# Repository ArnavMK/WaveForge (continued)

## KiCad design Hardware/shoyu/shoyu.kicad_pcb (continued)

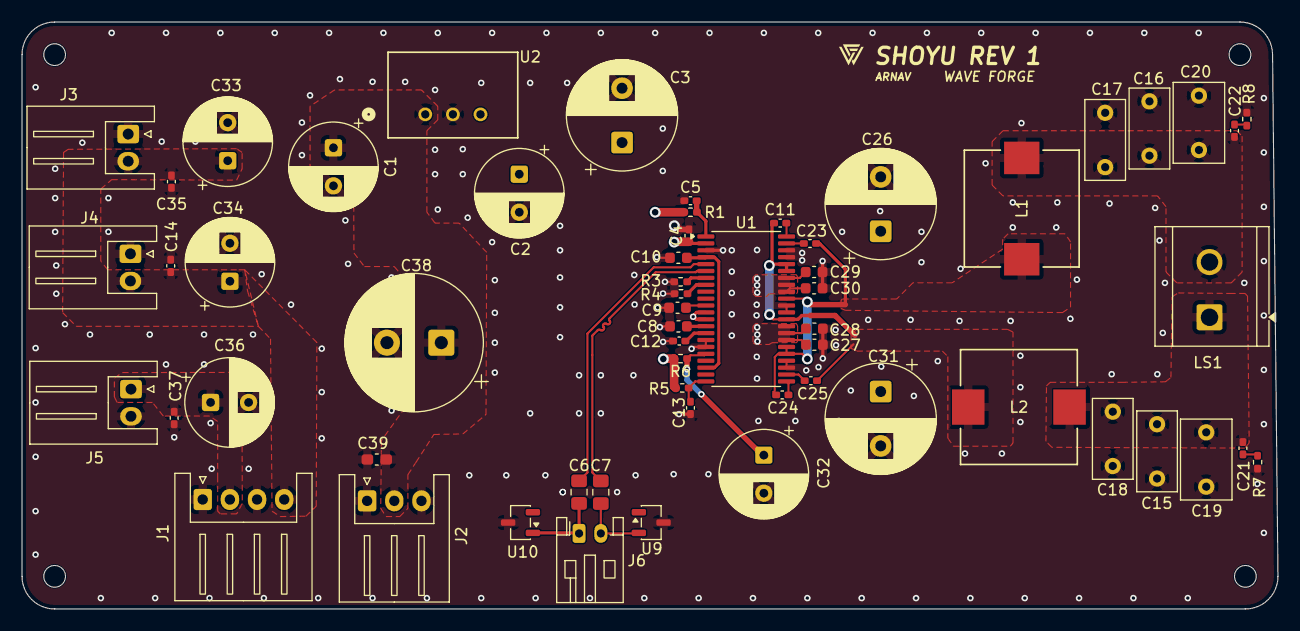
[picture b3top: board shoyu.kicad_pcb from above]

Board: 4 copper layers, 115.6 x 54.0 mm, 63 parts (0 on the bottom side), 28 nets.

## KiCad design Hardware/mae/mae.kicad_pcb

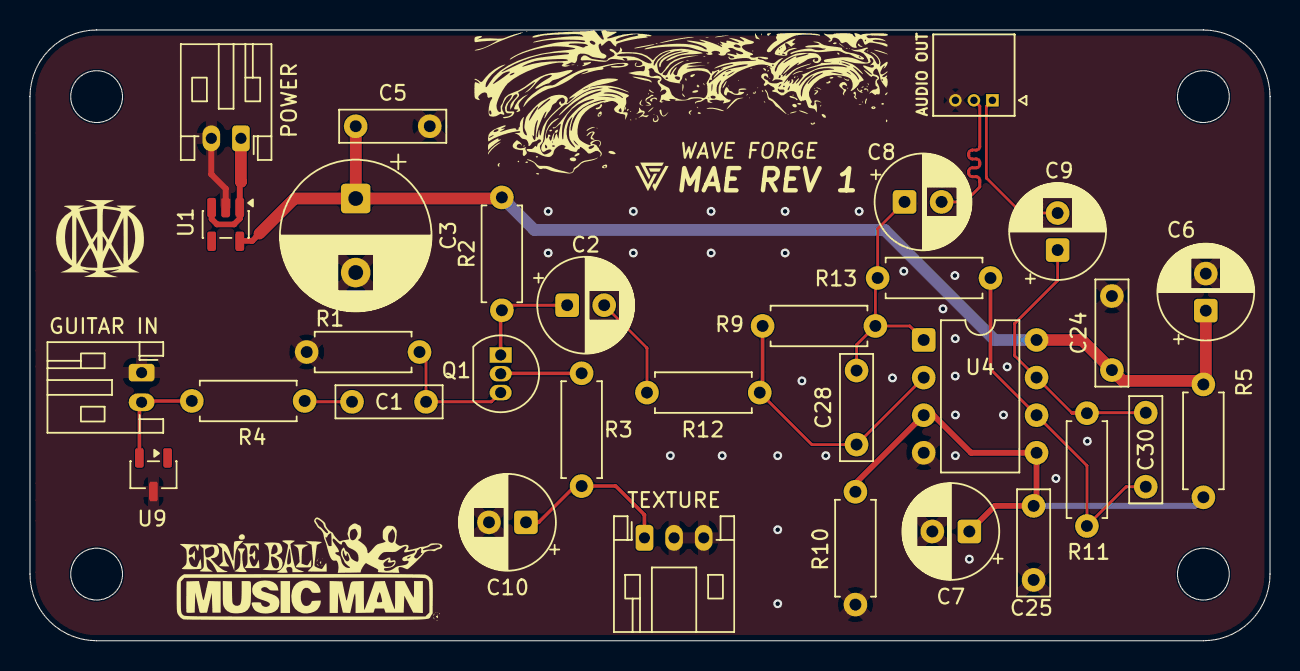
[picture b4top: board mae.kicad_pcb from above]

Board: 2 copper layers, 83.8 x 41.2 mm, 35 parts (0 on the bottom side), 17 nets.

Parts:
AUDIO OUT: 530480310; MOLEX_530480310
C1, C5, C24, C25: 100nF; C_Rect_L7.0mm_W2.0mm_P5.00mm
C2, C6, C7, C8, C9: 10uF; CP_Radial_D6.3mm_P2.50mm
C3: 100uF; CP_Radial_D10.0mm_P5.00mm
C10: c; CP_Radial_D6.3mm_P2.50mm
C28, C30: 100pF; C_Rect_L7.0mm_W2.0mm_P5.00mm
GUITAR IN: Guitar_IN; JST_PH_S2B-PH-K_1x02_P2.00mm_Horizontal
H3, H4, H5, H6: MountingHole; MountingHole_3.5mm
POWER: POWER_IN; JST_PH_S2B-PH-K_1x02_P2.00mm_Horizontal
Q1: Q_NJFET_DSG; TO-92_Inline
R1: 1MΩ; R_Axial_DIN0207_L6.3mm_D2.5mm_P7.62mm_Horizontal
R2, R3: R; R_Axial_DIN0207_L6.3mm_D2.5mm_P7.62mm_Horizontal
R4: 100Ω; R_Axial_DIN0207_L6.3mm_D2.5mm_P7.62mm_Horizontal
R5, R9, R10, R11, R12, R13: 10K; R_Axial_DIN0207_L6.3mm_D2.5mm_P7.62mm_Horizontal
TEXTURE: R_Potentiometer; JST_PH_S3B-PH-K_1x03_P2.00mm_Horizontal
U1: MAX40200AUK; SOT-23-5
U4: NE5532; DIP-8_W7.62mm
U9: SOT-23-3

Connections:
+9V: C3.1, C5.1, C6.1, C24.1, R2.2, R5.1, U1.5 (OUT), U4.8 (V+)
/AUDIO_OUT+: AUDIO OUT.2, C8.2
/AUDIO_OUT-: AUDIO OUT.1, C9.2
/DRAIN: C2.1, Q1.1 (D), R2.1
/GATE: C1.2, Q1.3 (G), R1.2
/PREAMP_OUT: C2.2, R12.1
/SOURCE: Q1.2 (S), R3.2
/U4A_AUDIO: C8.1, C28.2, R9.2, R13.1, U4.1
/VBIAS: C7.1, C25.1, R5.2, R10.2, U4.3 (+), U4.5 (+)
GND: AUDIO OUT.3, C3.2, C5.2, C6.2, C7.2, C10.2, C24.2, C25.2, GUITAR IN.1, POWER.2, R1.1, R10.1, TEXTURE.2, TEXTURE.3, U1.2 (GND), U4.4 (V-), U9.3 (GND)
unnamed: C1.1, R4.2
unnamed: C10.1, R3.1, TEXTURE.1
unnamed: C9.1, C30.2, R11.2, U4.7
unnamed: GUITAR IN.2, R4.1, U9.2 (IO2)
unnamed: POWER.1, U1.1 (VDD), U1.3 (EN)
unnamed: C28.1, R9.1, R12.2, U4.2 (-)
unnamed: C30.1, R11.1, R13.2, U4.6 (-)

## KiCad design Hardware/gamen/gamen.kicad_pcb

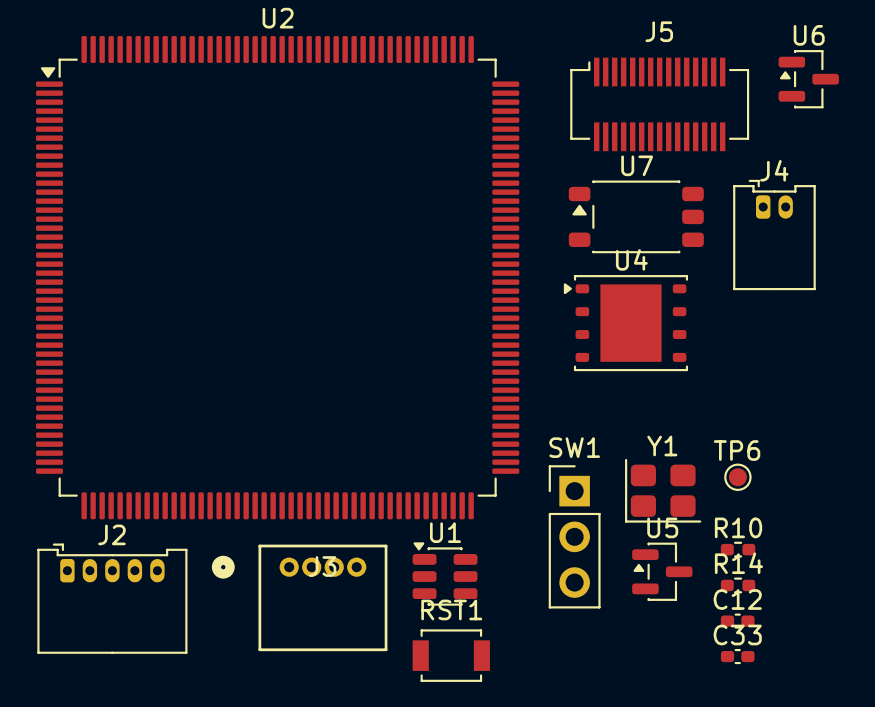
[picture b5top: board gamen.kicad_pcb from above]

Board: 6 copper layers, 19 parts (1 on the bottom side), 56 nets, no tracks yet.

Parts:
C12, C33: 100nF; C_0402_1005Metric_Pad0.74x0.62mm_HandSolder
J2: Conn_01x05_Pin; Molex_PicoBlade_53048-0510_1x05_P1.25mm_Horizontal
J3: UART_Header; CONN04_530480410_MOL
J4: MIDI CONN; Molex_PicoBlade_53048-0210_1x02_P1.25mm_Horizontal
J5: SCREEN CONN; Hirose_DF12_DF12C3.0-30DS-0.5V_2x15_P0.50mm_Vertical
R10, R14: 100Ω; R_0402_1005Metric_Pad0.72x0.64mm_HandSolder
RST1: SW_Push; SW_SPST_B3U-1000P
SW1: SW_SPDT; PinHeader_1x03_P2.54mm_Vertical
TP6: TP_UARTTX; TestPoint_Pad_D1.0mm
U1: TPS562201DDCR; SOT-23-6
U2: STM32H743IITx; LQFP-176_24x24mm_P0.5mm
U3: AS4C16M16SA-6TIN; TSOP-II-54_22.2x10.16mm_P0.8mm
U4: W25Q256JWPIQ; WSON-8-1EP_6x5mm_P1.27mm_EP3.4x4.3mm
U5, U6: SOT-23
U7: TLP2361(E; SO-5-6_4.55x3.7mm_P1.27mm
Y1: 25MHz; Crystal_SMD_WE_CFPX-180-4Pin_3.2x2.5mm

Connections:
+3.3V: C33.1, J2.5, J3.1, J5.4, SW1.3 (C), U2.6 (VBAT), U2.15 (VDD), U2.23 (VDD), U2.36 (VDD), U2.49 (VDD), U2.62 (VDD), U2.72 (VDD), U2.82 (VDD), U2.91 (VDD), U2.103 (VDD), U2.114 (VDD33_USB), U2.127 (VDD), U2.136 (VDD), U2.149 (VDD), U2.159 (VDD), U2.172 (VDD), U3.1 (VDD), U3.3 (VDDQ), U3.9 (VDDQ), U3.14 (VDD), U3.27 (VDD), U3.43 (VDDQ), U3.49 (VDDQ), U4.8 (VCC), U7.6 (VDD)
+3.3VA: U2.38 (VREF+), U2.39 (VDDA)
+5V: J5.1, J5.2, U1.3 (VIN), U1.5 (EN), U6.1 (IO1), U6.2 (IO2)
/MIDI_GND: J4.1, U7.3 (K)
/NRST: C12.1, J2.2, RST1.1, U2.31 (NRST)
/OSC_IN: U2.29 (PH0), Y1.3
/OSC_OUT: U2.30 (PH1), Y1.1
/QSPI_CLK: U2.28 (PF10), U4.6 (CLK)
/QSPI_IO0: U2.27 (PF9), U4.5 (DI/IO_{0})
/QSPI_IO1: U2.26 (PF8), U4.2 (DO/IO_{1})
/QSPI_IO2: U2.25 (PF7), U4.3 (~WP/IO_{2})
/QSPI_IO3: U2.24 (PF6), U4.7 (~HOLD/~RESET/IO_{3})
/SDNIS_RAS: U2.59 (PF11), U3.18 (*RAS)
/SDRAM_A0: U2.16 (PF0), U3.23 (A0)
/SDRAM_A1: U2.17 (PF1), U3.24 (A1)
/SDRAM_A2: U2.18 (PF2), U3.25 (A2)
/SDRAM_A3: U2.19 (PF3), U3.26 (A3)
/SDRAM_A4: U2.20 (PF4), U3.29 (A4)
/SDRAM_A5: U2.21 (PF5), U3.30 (A5)
/SDRAM_A6: U2.60 (PF12), U3.31 (A6)
/SDRAM_A7: U2.63 (PF13), U3.32 (A7)
/SDRAM_A8: U2.64 (PF14), U3.33 (A8)
/SDRAM_A9: U2.65 (PF15), U3.34 (A9)
/SDRAM_A10: U2.66 (PG0), U3.22 (A10/AP)
/SDRAM_A11: U2.67 (PG1), U3.35 (A11)
/SDRAM_A12: U2.106 (PG2), U3.36 (A12)
/SDRAM_BA0: U2.108 (PG4), U3.20 (BA0)
/SDRAM_BA1: U2.109 (PG5), U3.21 (BA1)
/SDRAM_CAS: U2.160 (PG15), U3.17 (*CAS)
/SDRAM_CKE: U2.35 (PC3_C), U3.37 (CKE)
/SDRAM_CLK: U2.112 (PG8), U3.38 (CLK)
/SDRAM_CS: U2.34 (PC2_C), U3.19 (*CS)
/SDRAM_DQ0: U2.104 (PD14), U2.142 (PD0), U3.2 (DQ0)
/SDRAM_DQ1: U2.105 (PD15), U3.4 (DQ1)
/SDRAM_DQ3: U2.143 (PD1), U3.7 (DQ3)
/SDRAM_DQ4: U2.70 (PE9), U3.8 (DQ4)
/SDRAM_DQ5: U2.69 (PE8), U3.10 (DQ5)
/SDRAM_DQ6: U2.68 (PE7), U3.11 (DQ6)
/SDRAM_DQ7: U2.73 (PE10), U3.13 (DQ7)
/SDRAM_DQ8: U2.74 (PE11), U3.42 (DQ8)
/SDRAM_DQ9: U2.75 (PE12), U3.44 (DQ9)
/SDRAM_DQ10: U2.76 (PE13), U3.45 (DQ10)
/SDRAM_DQ11: U2.77 (PE14), U3.47 (DQ11)
/SDRAM_DQ12: U2.78 (PE15), U3.48 (DQ12)
/SDRAM_DQ13: U2.96 (PD8), U3.50 (DQ13)
/SDRAM_DQ14: U2.97 (PD9), U3.51 (DQ14)
/SDRAM_DQ15: U2.98 (PD10), U3.53 (DQ15)
/SDRAM_NBL0: U2.169 (PE0), U3.15 (LDQM)
/SDRAM_NBL1: U2.170 (PE1), U3.39 (UDQM)
/SDRAM_WE: U2.32 (PC0), U3.16 (*WE)
/SWCLK: J2.3, U2.137 (PA14)
/SWDIO: J2.4, U2.124 (PA13)
/UART_RX: J3.3, R14.1, U2.93 (PB13), U5.2 (IO2)
/UART_TX: J3.2, R10.1, U2.92 (PB12), U5.1 (IO1)
/UART_TX_RES: R10.2, TP6.1 (1_1)
GND: C12.2, C33.2, J2.1, J3.4, J5.3, J5.29, RST1.2, SW1.1 (A), U1.1 (GND), U2.14 (VSS), U2.22 (VSS), U2.37 (VSSA), U2.48 (VSS), U2.61 (VSS), U2.71 (VSS), U2.90 (VSS), U2.102 (VSS), U2.113 (VSS), U2.126 (VSS), U2.135 (VSS), U2.148 (VSS), U2.158 (VSS), U3.6 (VSSQ), U3.12 (VSSQ), U3.28 (VSS), U3.41 (VSS), U3.46 (VSSQ), U3.52 (VSSQ), U3.54 (VSS), U4.4 (GND), U4.9 (EP), U5.3 (GND), U6.3 (GND), U7.4 (GND), Y1.2

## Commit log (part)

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2026-02-28 Shori schems rev A done
2026-03-02 Started General Component Layout
2026-03-02 Finished Layout on shori of digital components
2026-03-04 Analog side layout complete on shori
2026-03-04 Added Mounting holes and fixed Board outline issue
2026-03-04 Proper Border outline made for shori
2026-03-04 Routes Oscillator, Gamen and Programming header.
2026-03-05 Rough Analog Routing complete for shori
2026-03-08 started shori rev 2, new mcu and ldo
    changed the schems to accomodate new mcu and ldo. next will be the audio codec
2026-03-08 saved previous commit
2026-03-09 Rev 2 mcu data lines and new shoyu molex connectors
2026-03-10 Shori Rev 2 schems complete!!!!!!
    next is to add passive cvalues in the codec output filtering and assigning footprints
2026-03-10 Added footprints for shori rev 2
2026-03-10 New I2S2 Pinout and MCLK resistor added
2026-03-10 Fixed Stupid mistakes and began power and mcu layout
2026-03-12 Layout complete!!!!!!
    Next is setting up the board border and rounded corners, change the molex power connector to JST one. and start routing!!
2026-03-14 Routing and memes done!!
2026-03-14 Added flash sotrage, boot0 switch and nrst button in schems
2026-03-14 Fixed Boot0 switch
2026-03-14 Flash, boot0 switch, led, and nrst button routed. The board is done!
2026-03-15 Reddit images posted!
2026-03-27 Rev 3 changes: RC filters, Ideal diodes, electrical fixes, and their layout
2026-03-27 Power LED added on schems
2026-04-02 Rev 3 main changes completed!
2026-04-04 removed gamen power conn and layout clean up
2026-04-05 Started Mae Schematics!!
2026-04-06 Mae rev 1 schems done! power supply and audio out
2026-04-07 Mae footprints assigned, all through hole
2026-04-07 Mae layout and routing complete rev 1
2026-04-09 Mae: stiching vias added
2026-04-10 shori final touches!
2026-04-13 ongoing cart added
2026-04-13 Shori: cleaned up flash and added more BOM
2026-04-16 Shori: Final BOM touches
2026-04-18 Mae: polarised caps, new layout and prints
2026-04-27 Gen: PSU, rev 1 schems done, mae and shori orderd
2026-04-27 Gen: Rev 1 schem done, footprints assignment underway
2026-04-28 Gen: Layout rev 1 done and routing started
2026-04-29 Gen: Layout and routing complete rev 1
2026-05-01 digikey order sheet wave forge 1 added
2026-05-05 Shoyu: schems started, power input and output conns added
2026-05-05 Shoyu: Schems finished Footpritns added
2026-05-06 Shoyu: Layout complete
2026-05-06 Shoyu: Right side power zones finished.
2026-05-08 Shoyu: rev 1 routing complete
2026-05-08 Shoyu: New Film caps for output filter
2026-05-09 Gen: New Routing, More memes and better buck layouts (rev 2)
2026-05-10 Shori: rev 4 changes made in seperate folder for now
2026-05-11 Shorr rev 4 completed and gamen started
    Gamen is going to actually make me kill my self
2026-05-11 Gamen: Power supply done and mcu basics done in shcems with minor fix in shori
2026-05-11 GAMEN: Started SDRAM
2026-05-13 Gamen: Screen FPC connector added
2026-05-19 Gamen: Screen connected to mcu
2026-06-23 Remvoed 3.3V on shori UART and changed tantalum cap
2026-06-23 Created Gallery Folders
2026-06-24 New Gallery Images for Reddit
